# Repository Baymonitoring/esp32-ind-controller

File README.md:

# esp32-ind-controller
I am working on a small controller based on the esp32 for industrial purposes. This is my initial version and far from what would be considered an industrial controller.
My idea is to get the first pcb up and running with the most basic components required for some type of industrial control, such as controlling relays and reading inputs.

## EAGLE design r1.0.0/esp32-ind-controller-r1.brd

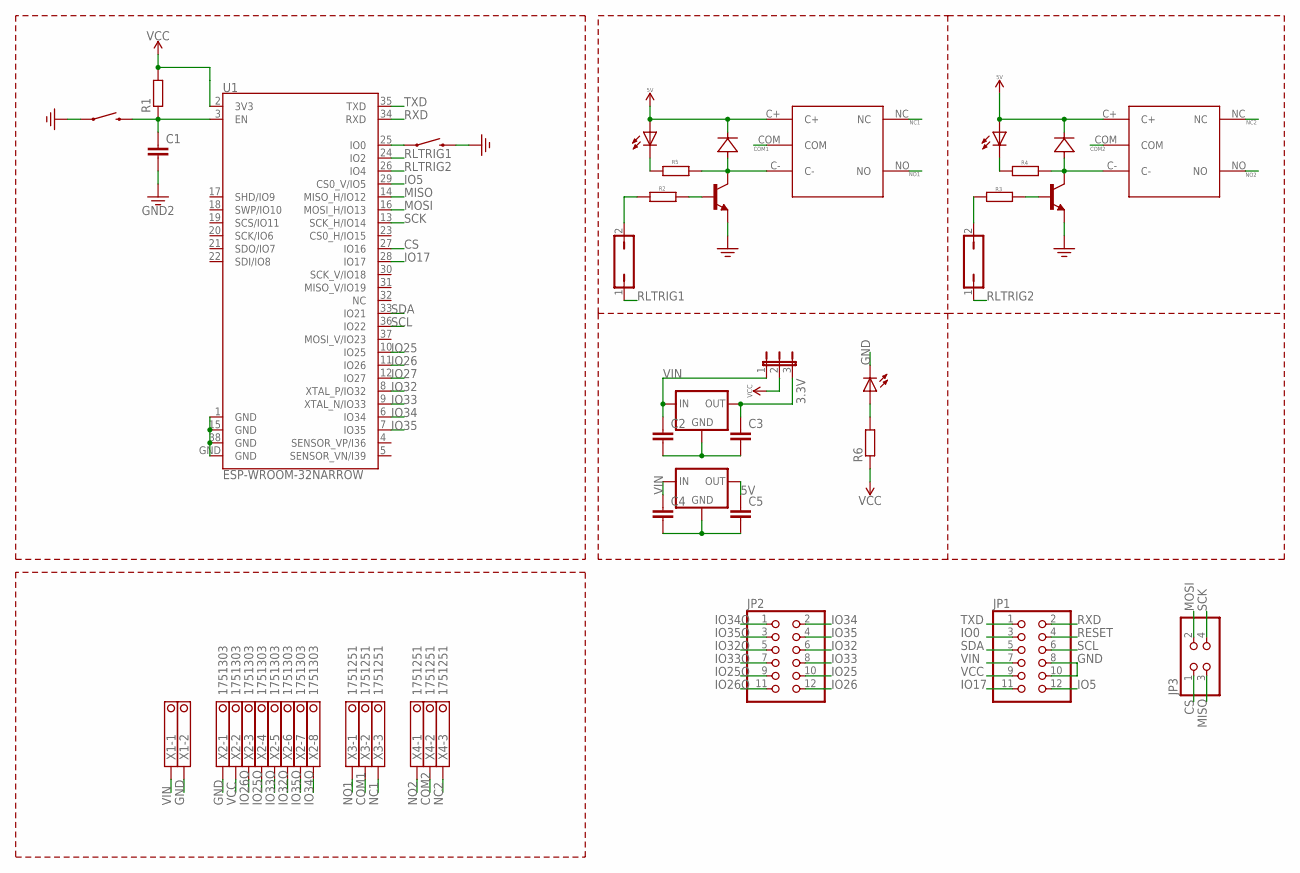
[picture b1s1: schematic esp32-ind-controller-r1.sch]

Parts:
C1, C2, C3, C4, C5: C1206
JP1, JP2: PINHD-2X6; 2X06
JP3: PINHD-2X2; 2X02
R1, R2, R3, R4, R5, R6: R1206
U1: ESP-WROOM-32NARROW; ESP-WROOM-32-NARROW
U$1, U$2: RELAY-SONGLE-05V
U$3, U$4: TACT-SW-SMD; TACTILE_SWITCH_SMD_6.0X3.5MM
U$5, U$8: MBR0520_DIODE; SOD123
U$6, U$7: MMBT3904_NPN_TRAN; SOT23
U$9, U$10, U$13: CHIPLED_1206GREEN; CHIPLED_1206_GRN
U$11: JP-2; JP2
U$12, U$14: LD1117-SOT223; SOT223
U$15, U$16: JP-1; JP1
X1: 1751248
X2: 1751303
X3, X4: 1751251

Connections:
3.3V: C3.1, U$11.3, U$12.2 (OUT), U$12.4 (OUT)
5V: C5.1, U$1.C+, U$2.C+, U$5.C, U$8.C, U$9.A, U$10.A, U$14.2 (OUT), U$14.4 (OUT)
COM1: U$1.COM, X3.2
COM2: U$2.COM, X4.2
CS: JP3.1, U1.27 (IO16)
GND: C1.2, C2.2, C3.2, C4.2, C5.2, JP1.8, JP1.10, U1.1 (GND), U1.15 (GND), U1.38 (GND), U1.GND, U$3.1, U$4.2, U$6.2 (E), U$7.2 (E), U$12.1 (GND), U$13.C, U$14.1 (GND), X1.2, X2.1
IO0: JP1.3, U1.25 (IO0), U$4.1
IO5: JP1.12, U1.29 (CS0_V/IO5)
IO17: JP1.11, U1.28 (IO17)
IO25: JP2.10, U1.10 (IO25)
IO25O: JP2.9, X2.4
IO26: JP2.12, U1.11 (IO26)
IO26O: JP2.11, X2.3
IO27: U1.12 (IO27)
IO32: JP2.6, U1.8 (XTAL_P/IO32)
IO32O: JP2.5, X2.6
IO33: JP2.8, U1.9 (XTAL_N/IO33)
IO33O: JP2.7, X2.5
IO34: JP2.2, U1.6 (IO34)
IO34O: JP2.1, X2.8
IO35: JP2.4, U1.7 (IO35)
IO35O: JP2.3, X2.7
MISO: JP3.3, U1.14 (MISO_H/IO12)
MOSI: JP3.2, U1.16 (MOSI_H/IO13)
unnamed: R6.2, U$13.A
unnamed: R5.1, U$1.C-, U$5.A, U$6.3 (C)
unnamed: R5.2, U$10.C
unnamed: R4.1, U$2.C-, U$7.3 (C), U$8.A
unnamed: R2.1, U$6.1 (B)
unnamed: R2.2, U$16.2
unnamed: R3.1, U$7.1 (B)
unnamed: R3.2, U$15.2
unnamed: R4.2, U$9.C
NC1: U$1.NC, X3.3
NC2: U$2.NC, X4.3
NO1: U$1.NO, X3.1
NO2: U$2.NO, X4.1
RESET: C1.1, JP1.4, R1.1, U1.3 (EN), U$3.2
RLTRIG1: U1.24 (IO2), U$16.1
RLTRIG2: U1.26 (IO4), U$15.1
RXD: JP1.2, U1.34 (RXD)
SCK: JP3.4, U1.13 (SCK_H/IO14)
SCL: JP1.6, U1.36 (IO22)
SDA: JP1.5, U1.33 (IO21)
TXD: JP1.1, U1.35 (TXD)
VCC: JP1.9, R1.2, R6.1, U1.2 (3V3), U$11.2, X2.2
VIN: C2.1, C4.1, JP1.7, U$11.1, U$12.3 (IN), U$14.3 (IN), X1.1

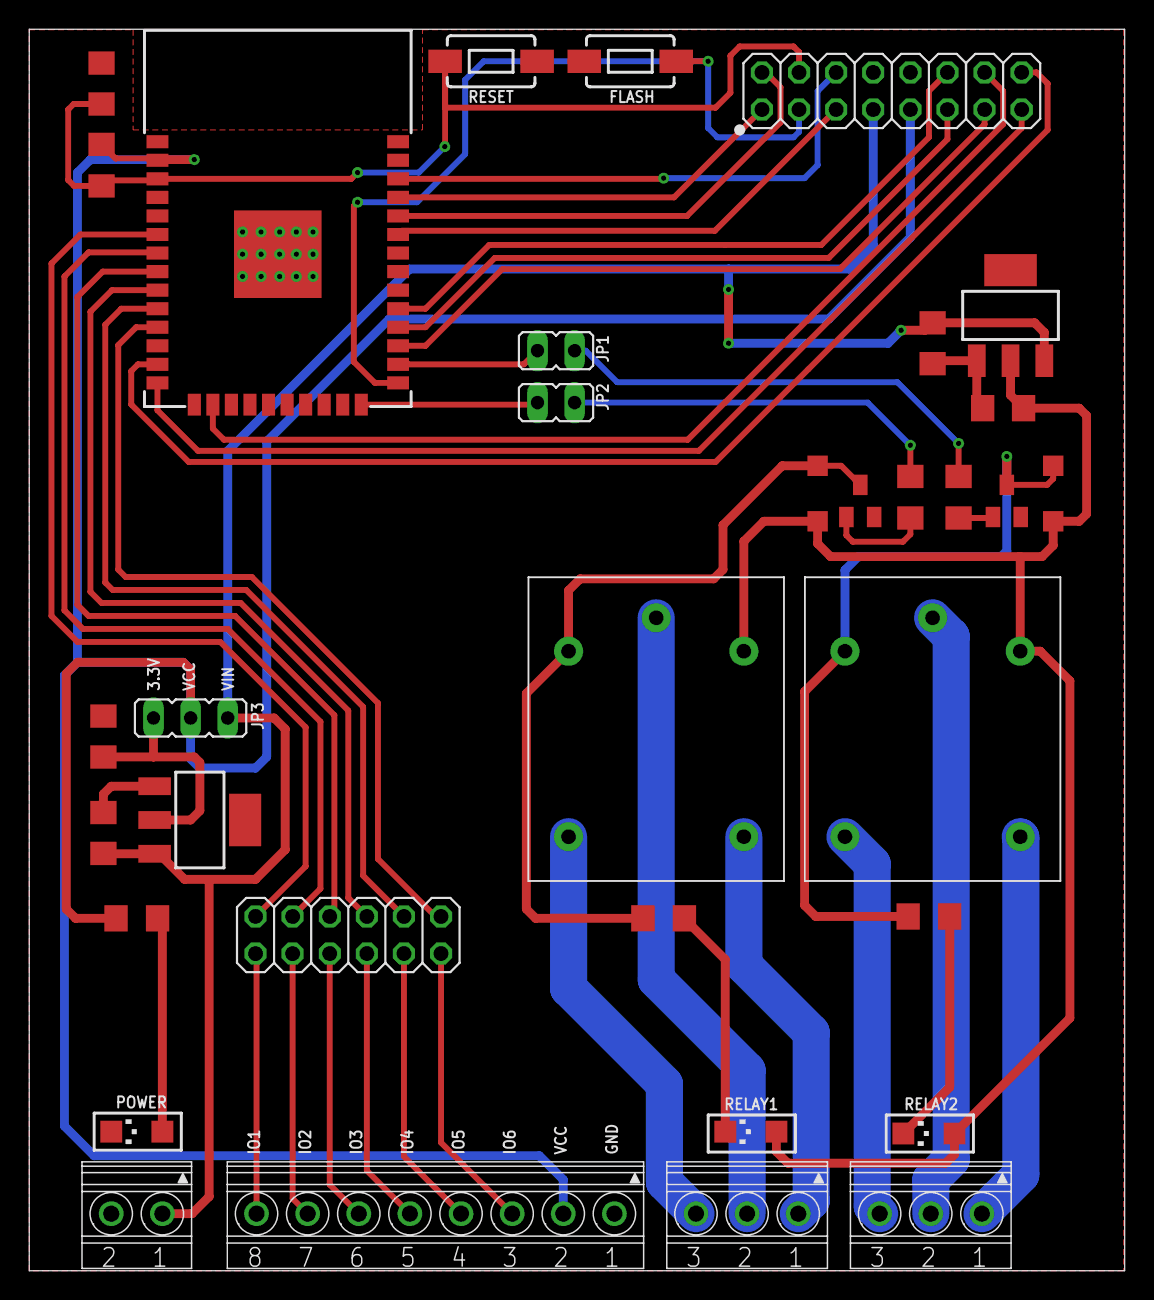
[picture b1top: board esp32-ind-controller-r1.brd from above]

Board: 2 copper layers, 75.0 x 85.0 mm, 35 parts (0 on the bottom side), 46 nets.

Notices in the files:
parts and their libraries:
SparkFun-PowerSymbols: Licensing: Creative Commons ShareAlike 4.0 International - https://creativecommons.org/licenses/by-sa/4.0
